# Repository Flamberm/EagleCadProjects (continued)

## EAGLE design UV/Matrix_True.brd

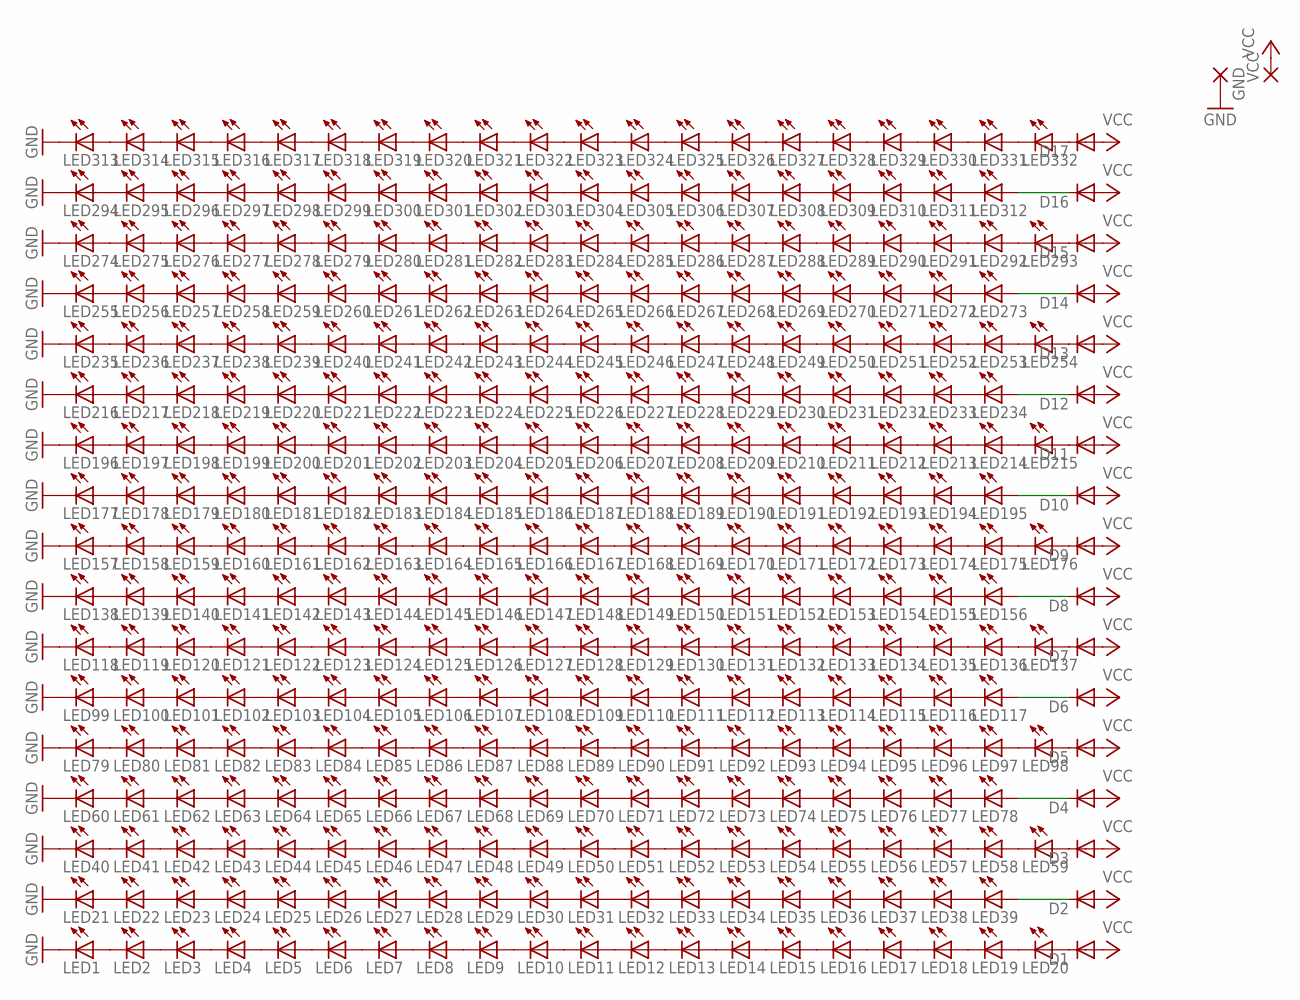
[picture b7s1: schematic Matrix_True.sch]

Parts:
D1, D2, D3, D4, D5, D6, D7, D8, D9, D10, D11, D12, D13, D14, D15, D16, D17: DIODE-SOD123; SOD123
GND: 3,17/1,3
LED1, LED2, LED3, LED4, LED5, LED6, LED7, LED8, LED9, LED10, LED11, LED12, LED13, LED14, LED15, LED16, LED17, LED18, LED19, LED20, LED21, LED22, LED23, LED24, LED25, LED26, LED27, LED28, LED29, LED30, LED31, LED32, LED33, LED34, LED35, LED36, LED37, LED38, LED39, LED40, LED41, LED42, LED43, LED44, LED45, LED46, LED47, LED48, LED49, LED50, LED51, LED52, LED53, LED54, LED55, LED56, LED57, LED58, LED59, LED60, LED61, LED62, LED63, LED64, LED65, LED66, LED67, LED68, LED69, LED70, LED71, LED72, LED73, LED74, LED75, LED76, LED77, LED78, LED79, LED80, LED81, LED82, LED83, LED84, LED85, LED86, LED87, LED88, LED89, LED90, LED91, LED92, LED93, LED94, LED95, LED96, LED97, LED98, LED99, LED100, LED101, LED102, LED103, LED104, LED105, LED106, LED107, LED108, LED109, LED110, LED111, LED112, LED113, LED114, LED115, LED116, LED117, LED118, LED119, LED120, LED121, LED122, LED123, LED124, LED125, LED126, LED127, LED128, LED129, LED130, LED131, LED132, LED133, LED134, LED135, LED136, LED137, LED138, LED139, LED140, LED141, LED142, LED143, LED144, LED145, LED146, LED147, LED148, LED149, LED150, LED151, LED152, LED153, LED154, LED155, LED156, LED157, LED158, LED159, LED160, LED161, LED162, LED163, LED164, LED165, LED166, LED167, LED168, LED169, LED170, LED171, LED172, LED173, LED174, LED175, LED176, LED177, LED178, LED179, LED180, LED181, LED182, LED183, LED184, LED185, LED186, LED187, LED188, LED189, LED190, LED191, LED192, LED193, LED194, LED195, LED196, LED197, LED198, LED199, LED200, LED201, LED202, LED203, LED204, LED205, LED206, LED207, LED208, LED209, LED210, LED211, LED212, LED213, LED214, LED215, LED216, LED217, LED218, LED219, LED220, LED221, LED222, LED223, LED224, LED225, LED226, LED227, LED228, LED229, LED230, LED231, LED232, LED233, LED234, LED235, LED236, LED237, LED238, LED239, LED240, LED241, LED242, LED243, LED244, LED245, LED246, LED247, LED248, LED249, LED250, LED251, LED252, LED253, LED254, LED255, LED256, LED257, LED258, LED259, LED260, LED261, LED262, LED263, LED264, LED265, LED266, LED267, LED268, LED269, LED270, LED271, LED272, LED273, LED274, LED275, LED276, LED277, LED278, LED279, LED280, LED281, LED282, LED283, LED284, LED285, LED286, LED287, LED288, LED289, LED290, LED291, LED292, LED293, LED294, LED295, LED296, LED297, LED298, LED299, LED300, LED301, LED302, LED303, LED304, LED305, LED306, LED307, LED308, LED309, LED310, LED311, LED312, LED313, LED314, LED315, LED316, LED317, LED318, LED319, LED320, LED321, LED322, LED323, LED324, LED325, LED326, LED327, LED328, LED329, LED330, LED331, LED332: LED5MM
VCC: 3,17/1,3

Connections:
GND: GND.1, LED1.K (C), LED21.K (C), LED40.K (C), LED60.K (C), LED79.K (C), LED99.K (C), LED118.K (C), LED138.K (C), LED157.K (C), LED177.K (C), LED196.K (C), LED216.K (C), LED235.K (C), LED255.K (C), LED274.K (C), LED294.K (C), LED313.K (C)
unnamed: LED1.A, LED2.K (C)
unnamed: LED2.A, LED3.K (C)
unnamed: LED3.A, LED4.K (C)
unnamed: LED4.A, LED5.K (C)
unnamed: LED5.A, LED6.K (C)
unnamed: LED6.A, LED7.K (C)
unnamed: LED7.A, LED8.K (C)
unnamed: LED8.A, LED9.K (C)
unnamed: LED9.A, LED10.K (C)
unnamed: LED10.A, LED11.K (C)
unnamed: LED11.A, LED12.K (C)
unnamed: LED12.A, LED13.K (C)
unnamed: LED13.A, LED14.K (C)
unnamed: LED14.A, LED15.K (C)
unnamed: LED15.A, LED16.K (C)
unnamed: LED16.A, LED17.K (C)
unnamed: LED17.A, LED18.K (C)
unnamed: LED18.A, LED19.K (C)
unnamed: LED19.A, LED20.K (C)
unnamed: D1.C, LED20.A
unnamed: LED21.A, LED22.K (C)
unnamed: LED22.A, LED23.K (C)
unnamed: LED23.A, LED24.K (C)
unnamed: LED24.A, LED25.K (C)
unnamed: LED25.A, LED26.K (C)
unnamed: LED26.A, LED27.K (C)
unnamed: LED27.A, LED28.K (C)
unnamed: LED28.A, LED29.K (C)
unnamed: LED29.A, LED30.K (C)
unnamed: LED30.A, LED31.K (C)
unnamed: LED31.A, LED32.K (C)
unnamed: LED32.A, LED33.K (C)
unnamed: LED33.A, LED34.K (C)
unnamed: LED34.A, LED35.K (C)
unnamed: LED35.A, LED36.K (C)
unnamed: LED36.A, LED37.K (C)
unnamed: LED37.A, LED38.K (C)
unnamed: LED38.A, LED39.K (C)
unnamed: D2.C, LED39.A
unnamed: LED40.A, LED41.K (C)
unnamed: LED41.A, LED42.K (C)
unnamed: LED42.A, LED43.K (C)
unnamed: LED43.A, LED44.K (C)
unnamed: LED44.A, LED45.K (C)
unnamed: LED45.A, LED46.K (C)
unnamed: LED46.A, LED47.K (C)
unnamed: LED47.A, LED48.K (C)
unnamed: LED48.A, LED49.K (C)
unnamed: LED49.A, LED50.K (C)
unnamed: LED50.A, LED51.K (C)
unnamed: LED51.A, LED52.K (C)
unnamed: LED52.A, LED53.K (C)
unnamed: LED53.A, LED54.K (C)
unnamed: LED54.A, LED55.K (C)
unnamed: LED55.A, LED56.K (C)
unnamed: LED56.A, LED57.K (C)
unnamed: LED57.A, LED58.K (C)
unnamed: LED58.A, LED59.K (C)
unnamed: D3.C, LED59.A
unnamed: LED60.A, LED61.K (C)
unnamed: LED61.A, LED62.K (C)
unnamed: LED62.A, LED63.K (C)
unnamed: LED63.A, LED64.K (C)
unnamed: LED64.A, LED65.K (C)
unnamed: LED65.A, LED66.K (C)
unnamed: LED66.A, LED67.K (C)
unnamed: LED67.A, LED68.K (C)
unnamed: LED68.A, LED69.K (C)
unnamed: LED69.A, LED70.K (C)
unnamed: LED70.A, LED71.K (C)
unnamed: LED71.A, LED72.K (C)
unnamed: LED72.A, LED73.K (C)
unnamed: LED73.A, LED74.K (C)
unnamed: LED74.A, LED75.K (C)
unnamed: LED75.A, LED76.K (C)
unnamed: LED76.A, LED77.K (C)
unnamed: LED77.A, LED78.K (C)
unnamed: D4.C, LED78.A
unnamed: LED79.A, LED80.K (C)
unnamed: LED80.A, LED81.K (C)
unnamed: LED81.A, LED82.K (C)
unnamed: LED82.A, LED83.K (C)
unnamed: LED83.A, LED84.K (C)
unnamed: LED84.A, LED85.K (C)
unnamed: LED85.A, LED86.K (C)
unnamed: LED86.A, LED87.K (C)
unnamed: LED87.A, LED88.K (C)
unnamed: LED88.A, LED89.K (C)
unnamed: LED89.A, LED90.K (C)
unnamed: LED90.A, LED91.K (C)
unnamed: LED91.A, LED92.K (C)
unnamed: LED92.A, LED93.K (C)
unnamed: LED93.A, LED94.K (C)
unnamed: LED94.A, LED95.K (C)
unnamed: LED95.A, LED96.K (C)
unnamed: LED96.A, LED97.K (C)
unnamed: LED97.A, LED98.K (C)
unnamed: D5.C, LED98.A
unnamed: LED99.A, LED100.K (C)
unnamed: LED100.A, LED101.K (C)
unnamed: LED101.A, LED102.K (C)
unnamed: LED102.A, LED103.K (C)
unnamed: LED103.A, LED104.K (C)
unnamed: LED104.A, LED105.K (C)
unnamed: LED105.A, LED106.K (C)
unnamed: LED106.A, LED107.K (C)
unnamed: LED107.A, LED108.K (C)
unnamed: LED108.A, LED109.K (C)
unnamed: LED109.A, LED110.K (C)
unnamed: LED110.A, LED111.K (C)
unnamed: LED111.A, LED112.K (C)
unnamed: LED112.A, LED113.K (C)
unnamed: LED113.A, LED114.K (C)
unnamed: LED114.A, LED115.K (C)
unnamed: LED115.A, LED116.K (C)
unnamed: LED116.A, LED117.K (C)
unnamed: D6.C, LED117.A
unnamed: LED118.A, LED119.K (C)
unnamed: LED119.A, LED120.K (C)
unnamed: LED120.A, LED121.K (C)
unnamed: LED121.A, LED122.K (C)
unnamed: LED122.A, LED123.K (C)
unnamed: LED123.A, LED124.K (C)
unnamed: LED124.A, LED125.K (C)
unnamed: LED125.A, LED126.K (C)
unnamed: LED126.A, LED127.K (C)
unnamed: LED127.A, LED128.K (C)
unnamed: LED128.A, LED129.K (C)
unnamed: LED129.A, LED130.K (C)
unnamed: LED130.A, LED131.K (C)
unnamed: LED131.A, LED132.K (C)
unnamed: LED132.A, LED133.K (C)
unnamed: LED133.A, LED134.K (C)
unnamed: LED134.A, LED135.K (C)
unnamed: LED135.A, LED136.K (C)
unnamed: LED136.A, LED137.K (C)
unnamed: D7.C, LED137.A
unnamed: LED138.A, LED139.K (C)
unnamed: LED139.A, LED140.K (C)
unnamed: LED140.A, LED141.K (C)
unnamed: LED141.A, LED142.K (C)
unnamed: LED142.A, LED143.K (C)
unnamed: LED143.A, LED144.K (C)
unnamed: LED144.A, LED145.K (C)
unnamed: LED145.A, LED146.K (C)
unnamed: LED146.A, LED147.K (C)
unnamed: LED147.A, LED148.K (C)
unnamed: LED148.A, LED149.K (C)
unnamed: LED149.A, LED150.K (C)
unnamed: LED150.A, LED151.K (C)
unnamed: LED151.A, LED152.K (C)
unnamed: LED152.A, LED153.K (C)
unnamed: LED153.A, LED154.K (C)
unnamed: LED154.A, LED155.K (C)
unnamed: LED155.A, LED156.K (C)
unnamed: D8.C, LED156.A
unnamed: LED157.A, LED158.K (C)
unnamed: LED158.A, LED159.K (C)
unnamed: LED159.A, LED160.K (C)
unnamed: LED160.A, LED161.K (C)
unnamed: LED161.A, LED162.K (C)
unnamed: LED162.A, LED163.K (C)
unnamed: LED163.A, LED164.K (C)
unnamed: LED164.A, LED165.K (C)
unnamed: LED165.A, LED166.K (C)
unnamed: LED166.A, LED167.K (C)
unnamed: LED167.A, LED168.K (C)
unnamed: LED168.A, LED169.K (C)
unnamed: LED169.A, LED170.K (C)
unnamed: LED170.A, LED171.K (C)
unnamed: LED171.A, LED172.K (C)
unnamed: LED172.A, LED173.K (C)
unnamed: LED173.A, LED174.K (C)
unnamed: LED174.A, LED175.K (C)
unnamed: LED175.A, LED176.K (C)
unnamed: D9.C, LED176.A
unnamed: LED177.A, LED178.K (C)
unnamed: LED178.A, LED179.K (C)
unnamed: LED179.A, LED180.K (C)
unnamed: LED180.A, LED181.K (C)
unnamed: LED181.A, LED182.K (C)
unnamed: LED182.A, LED183.K (C)
unnamed: LED183.A, LED184.K (C)
unnamed: LED184.A, LED185.K (C)
unnamed: LED185.A, LED186.K (C)
unnamed: LED186.A, LED187.K (C)
unnamed: LED187.A, LED188.K (C)
unnamed: LED188.A, LED189.K (C)
unnamed: LED189.A, LED190.K (C)
unnamed: LED190.A, LED191.K (C)
unnamed: LED191.A, LED192.K (C)
unnamed: LED192.A, LED193.K (C)
unnamed: LED193.A, LED194.K (C)
unnamed: LED194.A, LED195.K (C)
unnamed: D10.C, LED195.A
unnamed: LED196.A, LED197.K (C)
unnamed: LED197.A, LED198.K (C)
unnamed: LED198.A, LED199.K (C)
unnamed: LED199.A, LED200.K (C)
unnamed: LED200.A, LED201.K (C)
unnamed: LED201.A, LED202.K (C)
unnamed: LED202.A, LED203.K (C)
unnamed: LED203.A, LED204.K (C)
unnamed: LED204.A, LED205.K (C)
unnamed: LED205.A, LED206.K (C)
unnamed: LED206.A, LED207.K (C)
unnamed: LED207.A, LED208.K (C)
unnamed: LED208.A, LED209.K (C)
unnamed: LED209.A, LED210.K (C)
unnamed: LED210.A, LED211.K (C)
unnamed: LED211.A, LED212.K (C)
unnamed: LED212.A, LED213.K (C)
unnamed: LED213.A, LED214.K (C)
unnamed: LED214.A, LED215.K (C)
unnamed: D11.C, LED215.A
unnamed: LED216.A, LED217.K (C)
unnamed: LED217.A, LED218.K (C)
unnamed: LED218.A, LED219.K (C)
unnamed: LED219.A, LED220.K (C)
unnamed: LED220.A, LED221.K (C)
unnamed: LED221.A, LED222.K (C)
unnamed: LED222.A, LED223.K (C)
unnamed: LED223.A, LED224.K (C)
unnamed: LED224.A, LED225.K (C)
unnamed: LED225.A, LED226.K (C)
unnamed: LED226.A, LED227.K (C)
unnamed: LED227.A, LED228.K (C)
unnamed: LED228.A, LED229.K (C)
unnamed: LED229.A, LED230.K (C)
unnamed: LED230.A, LED231.K (C)
unnamed: LED231.A, LED232.K (C)
unnamed: LED232.A, LED233.K (C)
unnamed: LED233.A, LED234.K (C)
unnamed: D12.C, LED234.A
unnamed: LED235.A, LED236.K (C)
unnamed: LED236.A, LED237.K (C)
unnamed: LED237.A, LED238.K (C)
unnamed: LED238.A, LED239.K (C)
unnamed: LED239.A, LED240.K (C)
unnamed: LED240.A, LED241.K (C)
unnamed: LED241.A, LED242.K (C)
unnamed: LED242.A, LED243.K (C)
unnamed: LED243.A, LED244.K (C)
unnamed: LED244.A, LED245.K (C)
unnamed: LED245.A, LED246.K (C)
unnamed: LED246.A, LED247.K (C)
unnamed: LED247.A, LED248.K (C)
unnamed: LED248.A, LED249.K (C)
unnamed: LED249.A, LED250.K (C)
unnamed: LED250.A, LED251.K (C)
unnamed: LED251.A, LED252.K (C)
unnamed: LED252.A, LED253.K (C)
unnamed: LED253.A, LED254.K (C)
unnamed: D13.C, LED254.A
unnamed: LED255.A, LED256.K (C)
unnamed: LED256.A, LED257.K (C)
unnamed: LED257.A, LED258.K (C)
unnamed: LED258.A, LED259.K (C)
unnamed: LED259.A, LED260.K (C)
unnamed: LED260.A, LED261.K (C)
unnamed: LED261.A, LED262.K (C)
unnamed: LED262.A, LED263.K (C)
unnamed: LED263.A, LED264.K (C)
unnamed: LED264.A, LED265.K (C)
unnamed: LED265.A, LED266.K (C)
unnamed: LED266.A, LED267.K (C)
unnamed: LED267.A, LED268.K (C)
unnamed: LED268.A, LED269.K (C)
unnamed: LED269.A, LED270.K (C)
unnamed: LED270.A, LED271.K (C)
unnamed: LED271.A, LED272.K (C)
unnamed: LED272.A, LED273.K (C)
unnamed: D14.C, LED273.A
unnamed: LED274.A, LED275.K (C)
unnamed: LED275.A, LED276.K (C)
unnamed: LED276.A, LED277.K (C)
unnamed: LED277.A, LED278.K (C)
unnamed: LED278.A, LED279.K (C)
unnamed: LED279.A, LED280.K (C)
unnamed: LED280.A, LED281.K (C)
unnamed: LED281.A, LED282.K (C)
unnamed: LED282.A, LED283.K (C)
unnamed: LED283.A, LED284.K (C)
unnamed: LED284.A, LED285.K (C)
unnamed: LED285.A, LED286.K (C)
unnamed: LED286.A, LED287.K (C)
unnamed: LED287.A, LED288.K (C)
unnamed: LED288.A, LED289.K (C)
unnamed: LED289.A, LED290.K (C)
unnamed: LED290.A, LED291.K (C)
unnamed: LED291.A, LED292.K (C)
unnamed: LED292.A, LED293.K (C)
unnamed: D15.C, LED293.A
unnamed: LED294.A, LED295.K (C)
unnamed: LED295.A, LED296.K (C)
unnamed: LED296.A, LED297.K (C)
unnamed: LED297.A, LED298.K (C)
unnamed: LED298.A, LED299.K (C)
unnamed: LED299.A, LED300.K (C)
unnamed: LED300.A, LED301.K (C)
unnamed: LED301.A, LED302.K (C)
unnamed: LED302.A, LED303.K (C)
unnamed: LED303.A, LED304.K (C)
unnamed: LED304.A, LED305.K (C)
unnamed: LED305.A, LED306.K (C)
unnamed: LED306.A, LED307.K (C)
unnamed: LED307.A, LED308.K (C)
unnamed: LED308.A, LED309.K (C)
unnamed: LED309.A, LED310.K (C)
unnamed: LED310.A, LED311.K (C)
unnamed: LED311.A, LED312.K (C)
unnamed: D16.C, LED312.A
unnamed: LED313.A, LED314.K (C)
unnamed: LED314.A, LED315.K (C)
unnamed: LED315.A, LED316.K (C)
unnamed: LED316.A, LED317.K (C)
unnamed: LED317.A, LED318.K (C)
unnamed: LED318.A, LED319.K (C)
unnamed: LED319.A, LED320.K (C)
unnamed: LED320.A, LED321.K (C)
unnamed: LED321.A, LED322.K (C)
unnamed: LED322.A, LED323.K (C)
unnamed: LED323.A, LED324.K (C)
unnamed: LED324.A, LED325.K (C)
unnamed: LED325.A, LED326.K (C)
unnamed: LED326.A, LED327.K (C)
unnamed: LED327.A, LED328.K (C)
unnamed: LED328.A, LED329.K (C)
unnamed: LED329.A, LED330.K (C)
unnamed: LED330.A, LED331.K (C)
unnamed: LED331.A, LED332.K (C)
unnamed: D17.C, LED332.A
VCC: D1.A, D2.A, D3.A, D4.A, D5.A, D6.A, D7.A, D8.A, D9.A, D10.A, D11.A, D12.A, D13.A, D14.A, D15.A, D16.A, D17.A, VCC.1

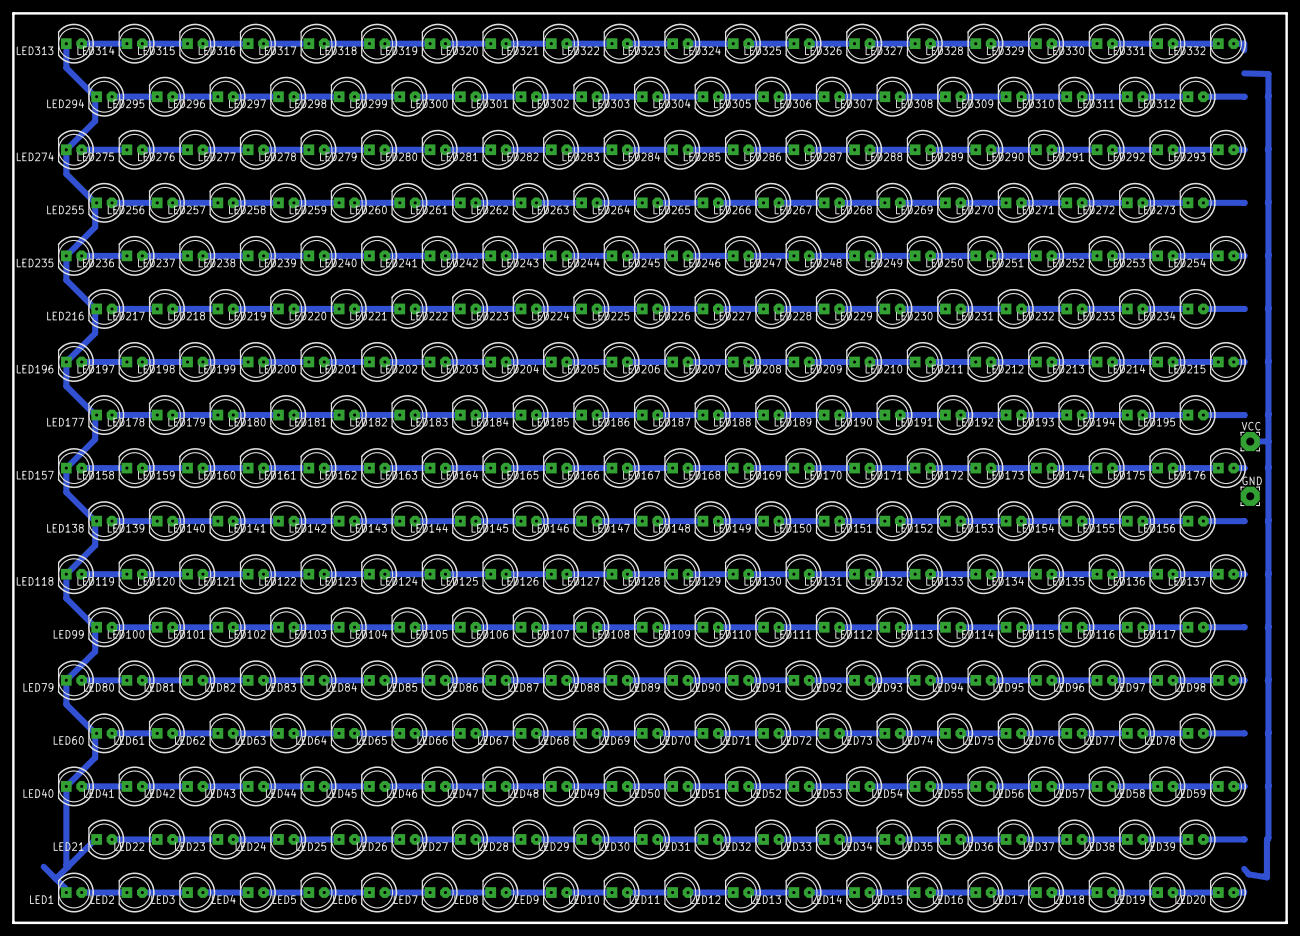
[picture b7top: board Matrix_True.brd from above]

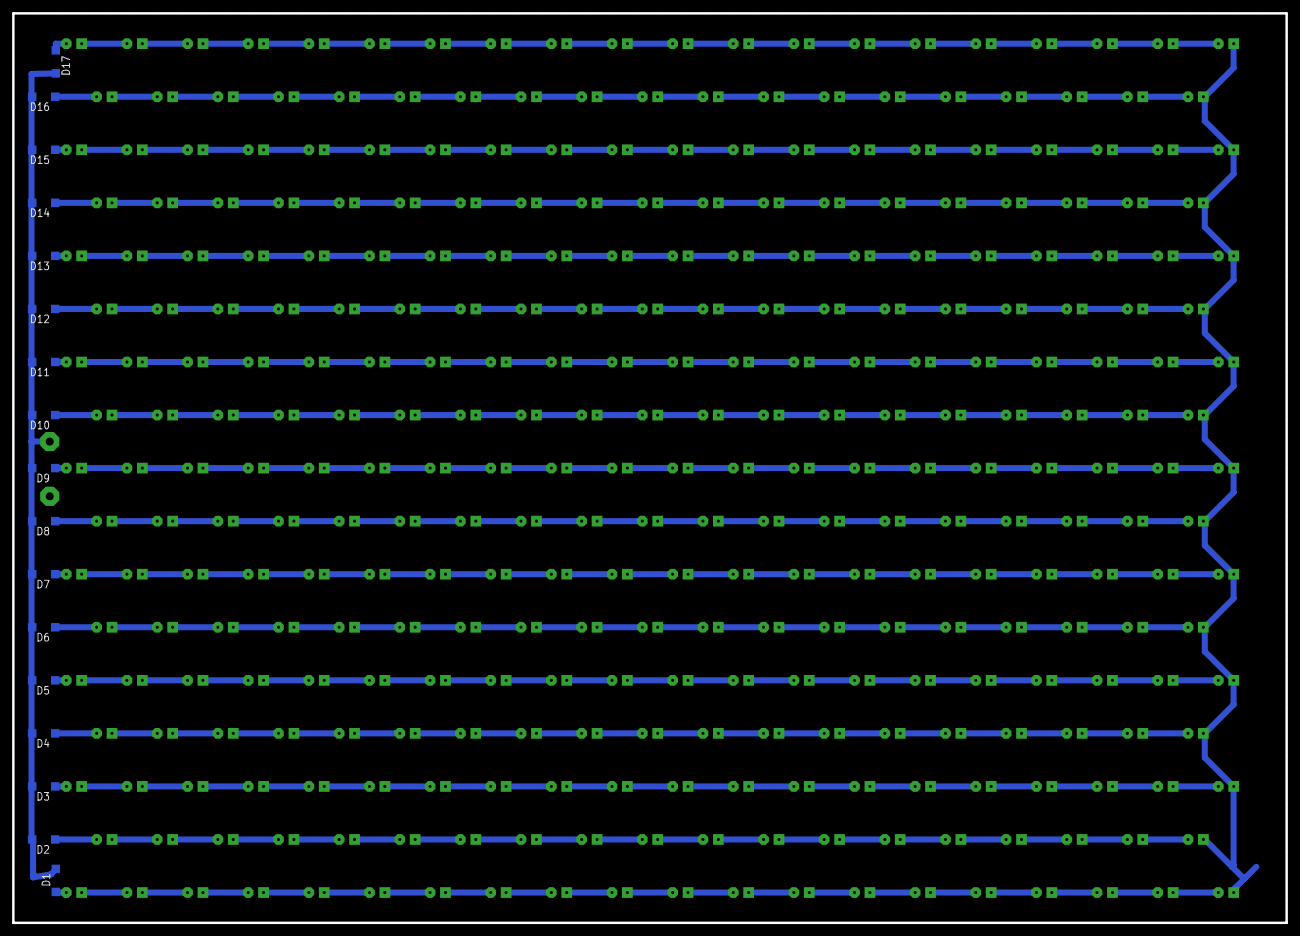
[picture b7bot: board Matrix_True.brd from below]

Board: 2 copper layers, 210.0 x 150.0 mm, 351 parts (17 on the bottom side), 334 nets.

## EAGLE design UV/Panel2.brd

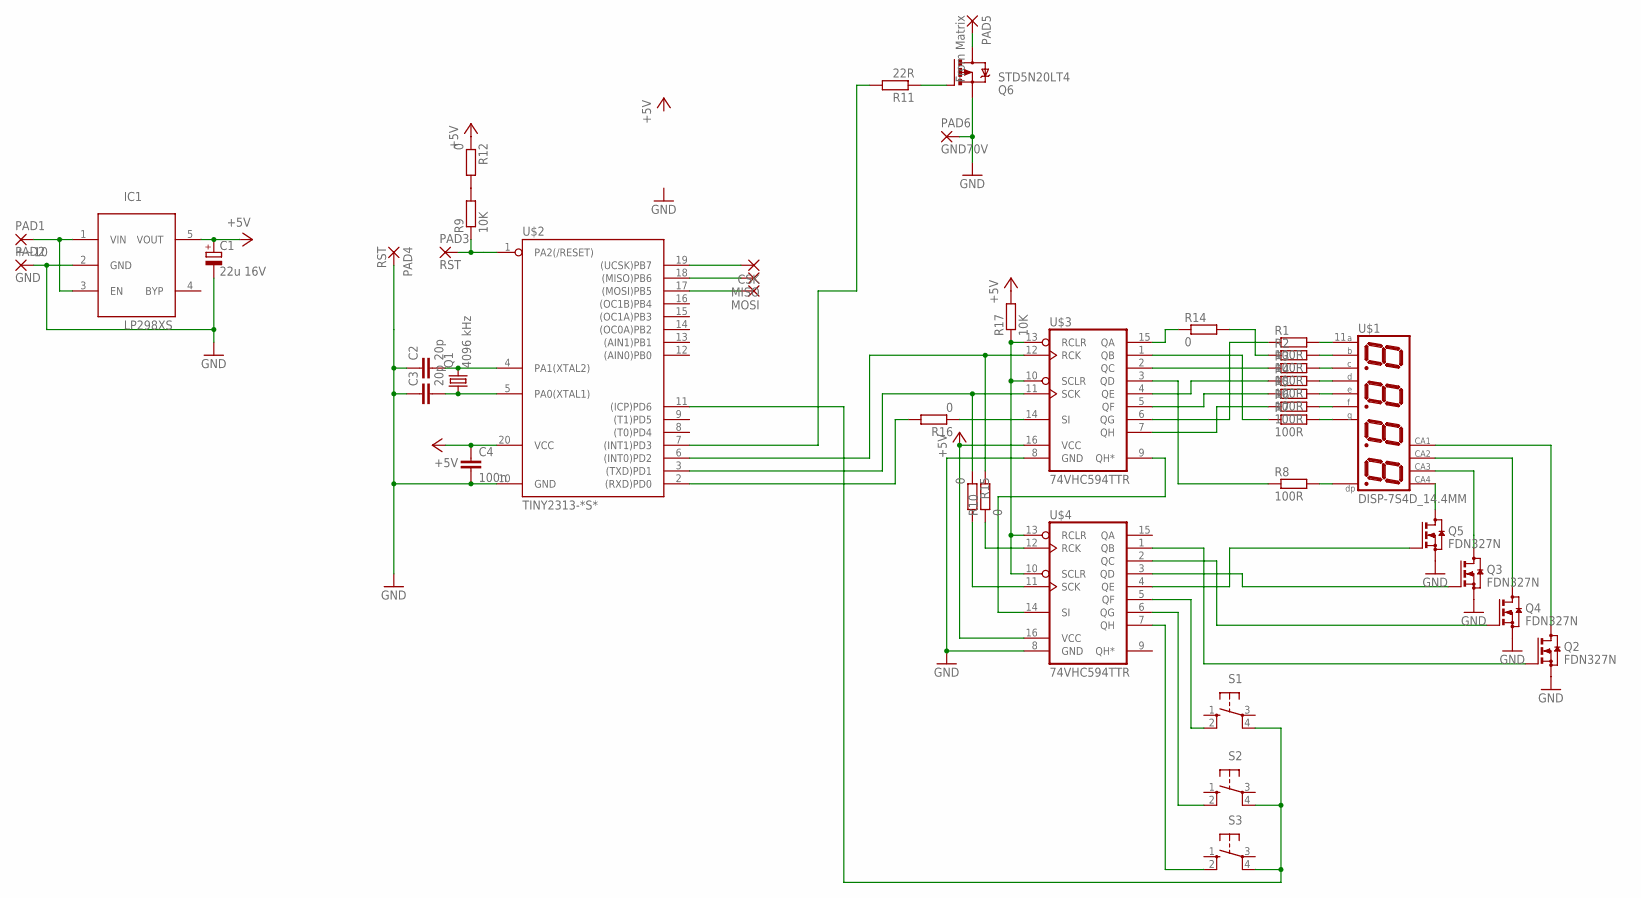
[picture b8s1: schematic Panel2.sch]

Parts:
C1: 22u 16V; SMC_B
C2, C3: 20p; C1206
C4: 100n; C1206
CSK: SMD2; SMD1,27-2,54
IC1: LP298XS; SOT23-5L
MISO: SMD2; SMD1,27-2,54
MOSI: SMD2; SMD1,27-2,54
PAD1: +~10; 5-2,5
PAD2: GND; 5-2,5
PAD3, PAD4: RST; SMD1,27-2,54
PAD5: From Matrix; SMD2,54-5,08
PAD6: GND70V; SMD2,54-5,08
Q1: 4096 kHz; HC49U-V
Q2, Q3, Q4, Q5: FDN327N; SOT23
Q6: STD5N20LT4; D-PAK_TO252AA
R1, R2, R3, R4, R5, R6, R7, R8: 100R; R1206
R9, R17: 10K; R1206
R10, R12, R14, R15, R16: 0; R1206
R11: 22R; R1206
S1, S2, S3: 40-XX; B3F-40XX
U$1: DISP-7S4D_14.4MM; DISP-7S4D
U$2: TINY2313-*S*; SO20L$
U$3, U$4: 74VHC594TTR; TSSOP16

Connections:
+5V: C1.+, C4.1, IC1.5 (VOUT), R12.1, R17.2, U$2.20 (VCC), U$3.16 (VCC), U$4.16 (VCC)
GND: C1.-, C2.1, C3.1, C4.2, IC1.2 (GND), PAD2.1, PAD4.1, PAD6.1, Q2.2 (S), Q3.2 (S), Q4.2 (S), Q5.2 (S), Q6.3 (S), U$2.10 (GND), U$3.8 (GND), U$4.8 (GND)
unnamed: R1.2, U$1.11 (A)
unnamed: R2.2, U$1.7 (B)
unnamed: Q5.3 (D), U$1.6 (С4)
unnamed: R3.2, U$1.4 (C)
unnamed: Q4.3 (D), U$1.9 (С2)
unnamed: R4.2, U$1.2 (D)
unnamed: R5.2, U$1.1 (E)
unnamed: R6.2, U$1.10 (F)
unnamed: R7.2, U$1.5 (G)
unnamed: R8.2, U$1.3 (DP)
unnamed: IC1.1 (VIN), IC1.3 (EN), PAD1.1
unnamed: C2.2, Q1.2, U$2.4 (PA1(XTAL2))
unnamed: C3.2, Q1.1, U$2.5 (PA0(XTAL1))
unnamed: PAD3.1, R9.1, U$2.1 (PA2(/RESET))
unnamed: Q2.3 (D), U$1.12 (С1)
unnamed: U$3.9 (QH*), U$4.14 (SI)
unnamed: R15.1, U$2.3 ((TXD)PD1), U$3.11 (SCK)
unnamed: R10.2, U$2.6 ((INT0)PD2), U$3.12 (RCK)
unnamed: R17.1, U$3.10 (SCLR), U$3.13 (RCLR), U$4.10 (SCLR), U$4.13 (RCLR)
unnamed: R14.1, U$3.15 (QA)
unnamed: Q2.1 (G), U$4.1 (QB)
unnamed: R10.1, U$4.12 (RCK)
unnamed: R15.2, U$4.11 (SCK)
unnamed: R16.1, U$3.14 (SI)
unnamed: R7.1, U$3.1 (QB)
unnamed: R3.1, U$3.2 (QC)
unnamed: R8.1, U$3.3 (QD)
unnamed: R4.1, U$3.4 (QE)
unnamed: R5.1, U$3.5 (QF)
unnamed: R1.1, U$3.6 (QG)
unnamed: CSK.1, U$2.19 ((UCSK)PB7)
unnamed: MISO.1, U$2.18 ((MISO)PB6)
unnamed: MOSI.1, U$2.17 ((MOSI)PB5)
unnamed: R6.1, U$3.7 (QH)
unnamed: R2.1, R14.2
unnamed: Q4.1 (G), U$4.2 (QC)
unnamed: Q3.1 (G), U$4.3 (QD)
unnamed: Q3.3 (D), U$1.8 (С3)
unnamed: Q5.1 (G), U$4.4 (QE)
unnamed: S1.2 (S1), U$4.5 (QF)
unnamed: Q6.1 (G), R11.1
unnamed: S2.2 (S1), U$4.6 (QG)
unnamed: S3.2 (S1), U$4.7 (QH)
unnamed: S1.4 (P1), S2.4 (P1), S3.4 (P1), U$2.11 ((ICP)PD6)
unnamed: R11.2, U$2.7 ((INT1)PD3)
unnamed: R16.2, U$2.2 ((RXD)PD0)
unnamed: PAD5.1, Q6.4 (D)
unnamed: R9.2, R12.2

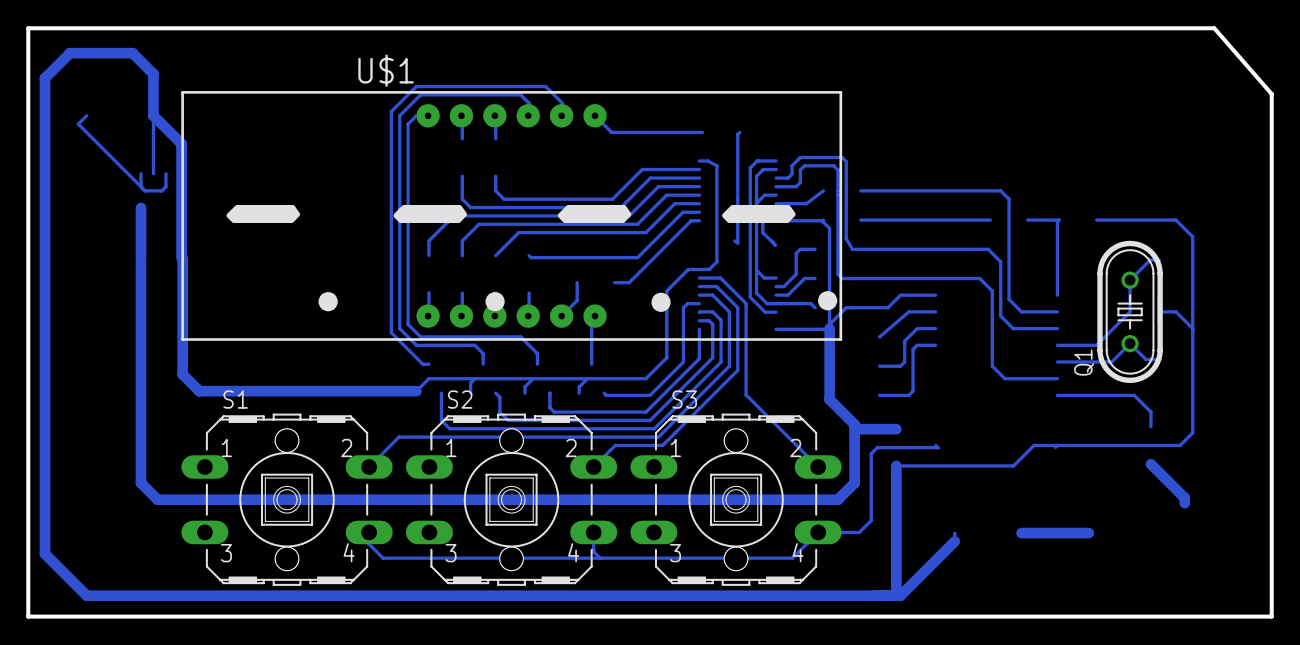
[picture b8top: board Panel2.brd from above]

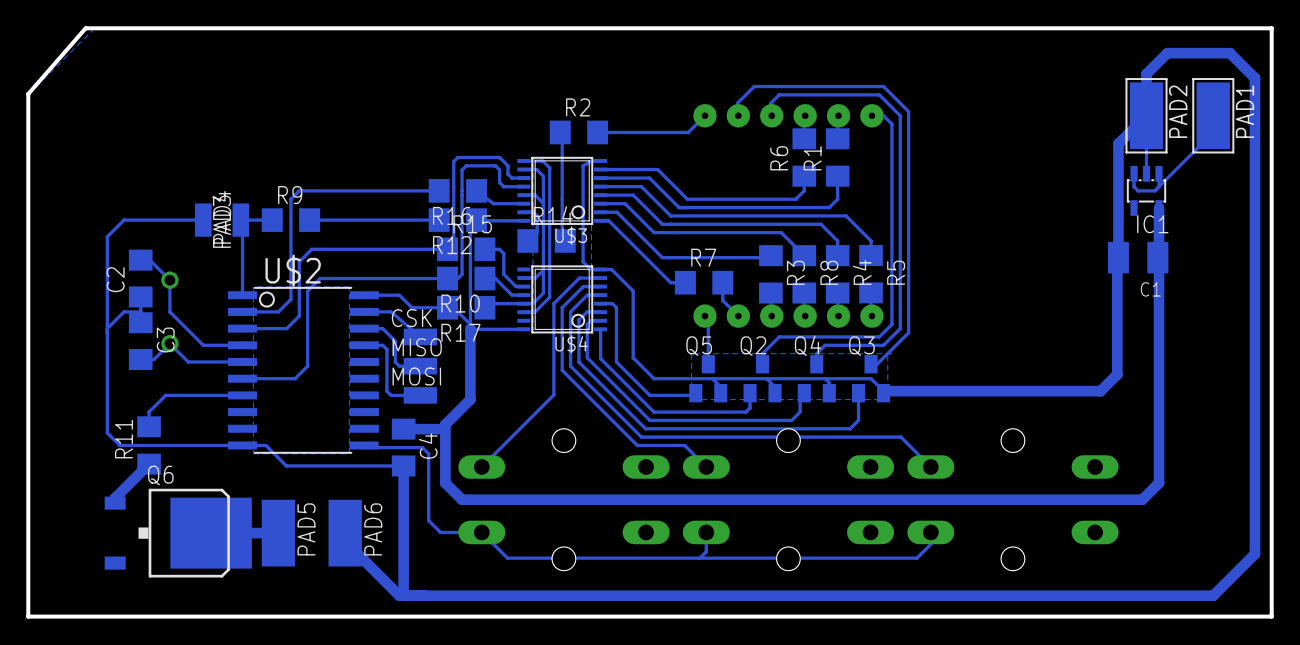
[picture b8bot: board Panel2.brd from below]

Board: 2 copper layers, 94.6 x 44.8 mm, 43 parts (38 on the bottom side), 50 nets.
